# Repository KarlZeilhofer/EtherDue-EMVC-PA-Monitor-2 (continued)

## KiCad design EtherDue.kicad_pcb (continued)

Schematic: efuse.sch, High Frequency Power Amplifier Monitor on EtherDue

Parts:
C1301, C1702, C1704: 100n/X7R; C_0603
C1705, C1706: 10n/X7R; C_0603
C1707, C1708: 1n/X7R; C_0805
C1709: DNP; C_0603
C1710: 1n/X7R; C_0603
JP1701: JUMPER3; Pin_Header_Straight_1x03
L1701: WE-CBF-742792093; R_0805
LED1701: RED; LED-0805
Q1701, Q1702: BSS123; sot23-gsd
Q1703, Q1704: BSS308; sot23-gsd
R1301: 10k; R_0603
R1302, R1703, R1707: 100R; R_0603
R1307: 2k2; R_0805
R1702, R1706: 4k7; R_0603
R1704: 1k; R_1206
R1708, R1709: 0R; R_0603
SW1301: SW_PUSH; SW_TACTILE_SMD
U1701: MCP6H04; SOIC-14_3.9x8.7mm_Pitch1.27mm
U1702: INA207; SOIC-14_3.9x8.7mm_Pitch1.27mm
U1703: MEU1S1212ZC; MEU1-Murata-DCDC
VR1701: 100k; Potentiometer_Bourns_3296W_3-8Zoll_Inline_ScrewUp

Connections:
/eFuse 1 (10A)/+Shunt: R1708.2; also elsewhere on the board
/eFuse 1 (10A)/-Shunt: R1709.2; also elsewhere on the board
/eFuse 1 (10A)/Comp+: U1702.2 (OUT), U1702.4 (CMP1_IN+); also elsewhere on the board
/eFuse 1 (10A)/Gate: C1707.1, C1710.1, U1703.4 (VOUT+); also elsewhere on the board
/eFuse 1 (10A)/LED_K: LED1701.K, R1704.2; also elsewhere on the board
/eFuse 1 (10A)/Source: C1708.1, C1710.2, U1703.3 (VOUT-); also elsewhere on the board
unnamed: C1705.1, C1709.1, R1708.1, U1702.14 (VIN+)
unnamed: C1706.1, C1709.2, R1709.1, U1702.13 (VIN-)
unnamed: C1707.2, L1701.1, U1703.2 (VIN+)
unnamed: L1701.2, Q1704.D
unnamed: Q1701.D, R1704.1
unnamed: Q1701.G, R1703.1
unnamed: Q1702.D, Q1704.G, R1706.1
unnamed: Q1703.D, Q1704.S
unnamed: Q1703.G, R1707.2
unnamed: R1702.2, U1702.5 (CMP2_IN-)
unnamed: R1703.2, R1707.1, U1702.11 (CMP1_OUT)
PIN24: JP1701.3; also elsewhere on the board

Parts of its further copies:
C1302, C1401, C1402, C1701, C1801, C1802, C1804, C1901, C1902, C1904: 100n/X7R; C_0603
C1805, C1806, C1905, C1906: 10n/X7R; C_0603
C1807, C1808, C1907, C1908: 1n/X7R; C_0805
C1809, C1909: DNP; C_0603
C1810, C1910: 1n/X7R; C_0603
JP1301, JP1401, JP1801, JP1901: JUMPER3; Pin_Header_Straight_1x03
L1801, L1901: WE-CBF-742792093; R_0805
LED1301, LED1401, LED1801, LED1901: RED; LED-0805
Q1301, Q1304, Q1401, Q1404, Q1801, Q1802, Q1901, Q1902: BSS123; sot23-gsd
Q1302, Q1303, Q1402, Q1403, Q1803, Q1804, Q1903, Q1904: BSS308; sot23-gsd
R1306, R1406, R1808, R1809, R1908, R1909: 0R; R_0603
R1308, R1408, R1705, R1803, R1805, R1807, R1903, R1905, R1907: 100R; R_0603
R1309, R1409, R1804, R1904: 1k; R_1206
R1407, R1710, R1810, R1910: 2k2; R_0805
R1701, R1801, R1901: 10k; R_0603
R1802, R1806, R1902, R1906: 4k7; R_0603
SW1401, SW1701, SW1801, SW1901: SW_PUSH; SW_TACTILE_SMD
U1403, U1802, U1902: MEU1S1212ZC; MEU1-Murata-DCDC
U1801, U1901: INA207; SOIC-14_3.9x8.7mm_Pitch1.27mm
VR1801, VR1901: 100k; Potentiometer_Bourns_3296W_3-8Zoll_Inline_ScrewUp

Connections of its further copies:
/Analog I/O/VIN1: R1306.2; also elsewhere on the board
/Analog I/O/VIN3: R1406.2; also elsewhere on the board
/eFuse 1 (10A)/Gate: R1710.2; also elsewhere on the board
/eFuse 1 (10A)/Source: R1710.1; also elsewhere on the board
/eFuse 2 (10A)/+Shunt: R1808.2; also elsewhere on the board
/eFuse 2 (10A)/-Shunt: R1809.2; also elsewhere on the board
/eFuse 2 (10A)/Comp+: U1801.2 (OUT), U1801.4 (CMP1_IN+); also elsewhere on the board
/eFuse 2 (10A)/Gate: C1807.1, C1810.1, R1810.2, U1802.4 (VOUT+); also elsewhere on the board
/eFuse 2 (10A)/LED_K: LED1801.K, R1804.2; also elsewhere on the board
/eFuse 2 (10A)/Reset\: R1801.2, SW1801.2, U1801.8 (CMP1_RESET\); also elsewhere on the board
/eFuse 2 (10A)/Source: C1808.1, C1810.2, R1810.1, U1802.3 (VOUT-); also elsewhere on the board
/eFuse 3 (60A)/+Shunt: R1908.2; also elsewhere on the board
/eFuse 3 (60A)/-Shunt: R1909.2; also elsewhere on the board
/eFuse 3 (60A)/Comp+: U1901.4 (CMP1_IN+); also elsewhere on the board
/eFuse 3 (60A)/Gate: C1907.1, C1910.1, R1910.2, U1902.4 (VOUT+); also elsewhere on the board
/eFuse 3 (60A)/ISense: U1901.2 (OUT); also elsewhere on the board
/eFuse 3 (60A)/LED_K: LED1901.K, R1904.2; also elsewhere on the board
/eFuse 3 (60A)/Reset\: R1901.2, SW1901.2, U1901.8 (CMP1_RESET\); also elsewhere on the board
/eFuse 3 (60A)/Source: C1908.1, C1910.2, R1910.1, U1902.3 (VOUT-); also elsewhere on the board
unnamed 184: R1306.1; also elsewhere on the board
unnamed 185: C1401.1, C1402.1; also elsewhere on the board
unnamed 192: R1406.1; also elsewhere on the board
unnamed 200: C1801.1, VR1801.2; also elsewhere on the board
unnamed: C1805.1, C1809.1, R1808.1, U1801.14 (VIN+)
unnamed: C1806.1, C1809.2, R1809.1, U1801.13 (VIN-)
unnamed: C1807.2, L1801.1, U1802.2 (VIN+)
unnamed: C1905.1, C1909.1, R1908.1, U1901.14 (VIN+)
unnamed: C1906.1, C1909.2, R1909.1, U1901.13 (VIN-)
unnamed: C1907.2, L1901.1, U1902.2 (VIN+)
unnamed: JP1801.2, R1805.1
unnamed: JP1901.2, R1905.1
unnamed: L1801.2, Q1804.D
unnamed: L1901.2, Q1904.D
unnamed: Q1801.D, R1804.1
unnamed: Q1801.G, R1803.1
unnamed: Q1802.D, Q1804.G, R1806.1
unnamed: Q1802.G, R1805.2
unnamed: Q1803.D, Q1804.S
unnamed: Q1803.G, R1807.2
unnamed: Q1901.D, R1904.1
unnamed: Q1901.G, R1903.1
unnamed: Q1902.D, Q1904.G, R1906.1
unnamed: Q1902.G, R1905.2
unnamed: Q1903.D, Q1904.S
unnamed: Q1903.G, R1907.2
unnamed: R1802.2, U1801.5 (CMP2_IN-)
unnamed: R1803.2, R1807.1, U1801.11 (CMP1_OUT)
unnamed: R1902.2, U1901.5 (CMP2_IN-)
unnamed: R1903.2, R1907.1, U1901.11 (CMP1_OUT)
unnamed 356: U1801.3 (CMP1_IN-/0.6V_REF); also elsewhere on the board
PIN24: JP1801.3, JP1901.3; also elsewhere on the board

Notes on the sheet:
12V/12V
10-turn potentiometer
Decoupling C is on parent sheet

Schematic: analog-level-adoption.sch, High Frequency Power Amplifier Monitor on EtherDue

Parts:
C2001, C2002, C2003, C2010, C2011, C2012: 10n/X7R; C_0603
C2004, C2005, C2006, C2007, C2008, C2009, C2013, C2014: 1n/X7R; C_0603
D2001, D2002, D2003, D2004: BAT54S; sot23
R2001, R2002, R2003: 47k; R_0805
R2004, R2005, R2006: 2k7; R_0603
R2007, R2008, R2009: 10k; R_0603
R2010, R2011: 6k8; R_0603
R2012: TBD; R_0603

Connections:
/Analog I/O/+3V3: C2004.1, C2006.1, C2008.1, C2013.1, D2001.3 (cathode), D2002.3 (cathode), D2003.3 (cathode), D2004.3 (cathode); also elsewhere on the board
/Analog Level Adoption/I_Fuse1_Out: C2010.1, R2007.2, R2010.2; also elsewhere on the board
/Analog Level Adoption/I_Fuse2_Out: C2011.1, R2008.2, R2011.2; also elsewhere on the board
/eFuse 1 (10A)/Comp+: R2007.1; also elsewhere on the board
/eFuse 1 (10A)/Source: R2001.1; also elsewhere on the board
/eFuse 2 (10A)/Comp+: R2008.1; also elsewhere on the board
/eFuse 2 (10A)/Source: R2002.1; also elsewhere on the board
/eFuse 3 (60A)/ISense: R2009.1; also elsewhere on the board
/eFuse 3 (60A)/Source: R2003.1; also elsewhere on the board
AD2: C2001.1, C2004.2, C2005.1, D2001.2 (AK), R2001.2, R2004.2; also elsewhere on the board
AD3: C2002.1, C2006.2, C2007.1, D2002.2 (AK), R2002.2, R2005.2; also elsewhere on the board
AD4: C2003.1, C2008.2, C2009.1, D2003.2 (AK), R2003.2, R2006.2; also elsewhere on the board
AD5: C2012.1, C2013.2, C2014.1, D2004.2 (AK), R2009.2, R2012.2; also elsewhere on the board

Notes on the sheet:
Voltages from 60V to 3.3V
Currents of F1 and F2 from 12V to 5V and of F3 from 12V to 3.3V
0...5V
0...3.3V
0...60V
0...12V
place this 1nF near ADC
to VIN0
to VIN2

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
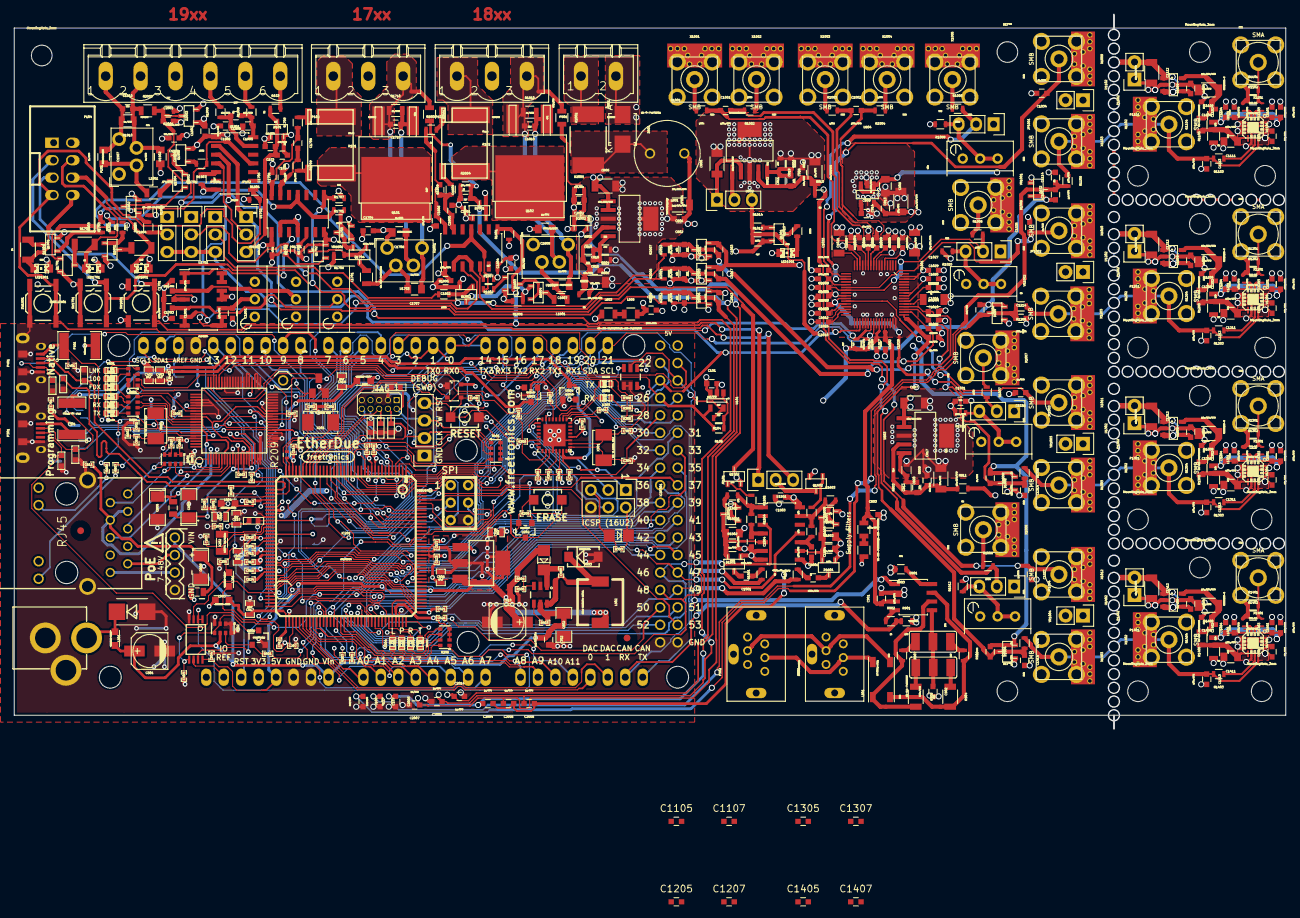
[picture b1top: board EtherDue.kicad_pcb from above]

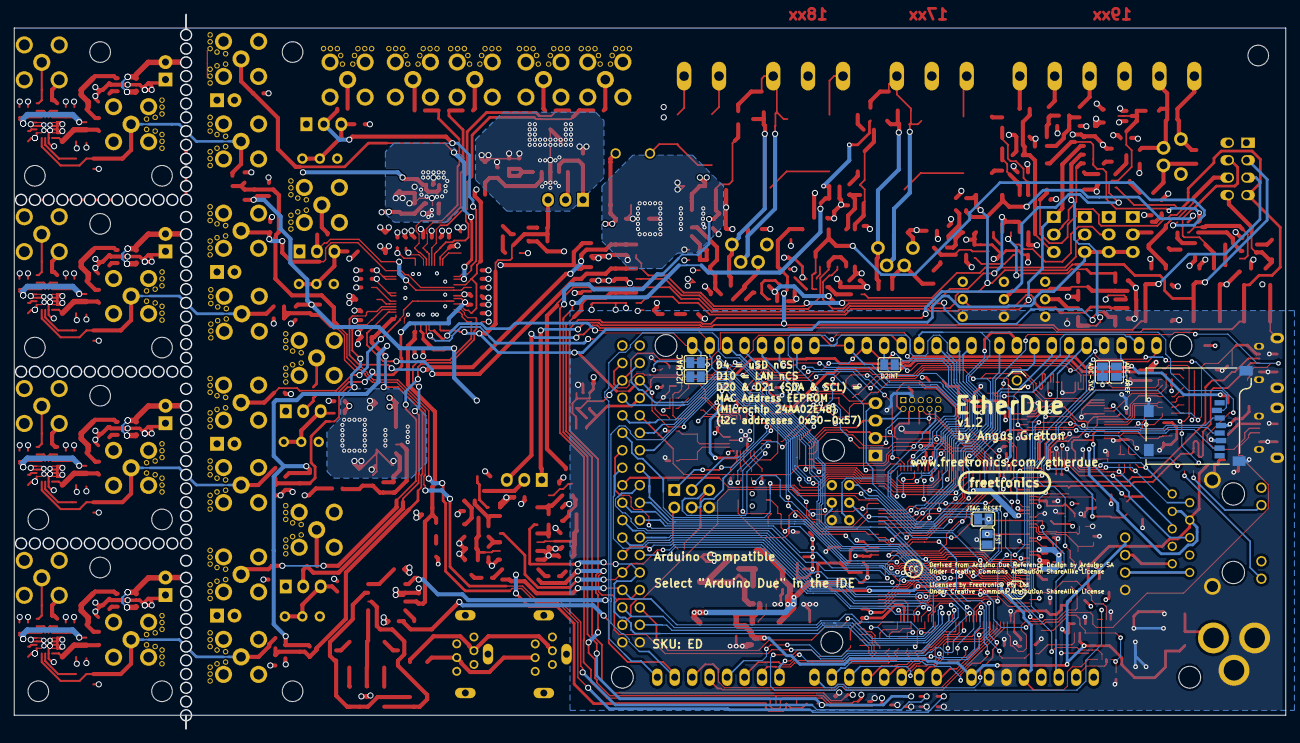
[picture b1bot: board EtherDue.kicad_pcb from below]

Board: 4 copper layers, 185.0 x 104.0 mm, 601 parts (10 on the bottom side), 372 nets.

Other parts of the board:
FIDUCIAL: val**; FIDUCIAL
FIDUCIAL#2: val**; FIDUCIAL
LOGO_CC: VAL**; LOGO_CC
LOGO_FREETRONICS: val**; LOGO_FREETRONICS
LOGO_FREETRONICS_SMALL: val**; LOGO_FREETRONICS_SMALL
MountingHole_3mm, MountingHole_3mm#2, MountingHole_3mm#3, MountingHole_3mm#4, MountingHole_3mm#5, MountingHole_3mm#6, MountingHole_3mm#7, MountingHole_3mm#8, MountingHole_3mm#9, MountingHole_3mm#10, MountingHole_3mm#11, MountingHole_3mm#12, MountingHole_3mm#13: VAL**; MountingHole_3mm

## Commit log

2015-04-08 nearly finished routing
2015-04-14 just before finishing DRC errors
2015-04-14 finished PCB layout, ready for review
2015-04-16 added all non-default libs into /libs and changed accordingly fp-lib-table and and the libs in EtherDue.pro. The project should now be a closed package.
2015-04-16 exported cmp-file from PCB and back imported it into the schematic. then exported BOM with kicad2csvbom tool
2015-05-13 Updates im Zuge des Tutorials

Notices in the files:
EtherDue.kicad_pcb:
Under Creative Commons Attribution ShareAlike License
Licensed by Freetronics Pty Ltd
analog-level-adoption.sch:
Derived from EtherDue - (C) 2014 Freetronics Pty Ltd
Licensed under Creative Commons Share-Alike
